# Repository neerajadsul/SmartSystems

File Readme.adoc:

# Temperature, Humidity, Ambient Light Monitoring
ifdef::env-name[:relfilesuffix: .adoc]

The goal of this project is to design a temperature and humidity monitoring system for indoor home usage.

## Specifications
. Monitor the temperature (T) in deg celsius with accuracy of better than 1%.
. Monitor the humidity (RH) in %RH (relative humidity) with accuracy of better than 5%.
. Monitor the ambient light in relative lux (LUX) with respect to dark.
. Capable of recording the T, RH, LUX at least once every 30 seconds.
. Records T, RH, LUX in a database.
. Presents T, RH, LUX data as a time-series via a web-interface.
. The web-interface is accesible atleast within the intra-net.

## System Design
A block diamgram of the system is shown in the figure below.

image::SensorNetwork/figures/SystemBlockDiagram.svg[Home Monitoring Systems Block Diagram]

## Hardware Design
The sensor board has Sensirion SHTC3 temperature and humidity sensor.
The board is designed to fit on top or under of the Raspberry Pi Pico W (PicoW).

image::SensorNetwork/figures/board_views.svg["Sensorboard for Temperature, Humidity and Ambient Light"]

## Software Design

### Monitoring Server
The monitoring server is deployed on a Raspberry Pi 400.
The sensor node communicates to a Python Django based web-app which can receive data on port 8080.
The web app stores data in a SQLite database. The database backup is scheduled for everyday on a internal network attached storage.

#### Web API Specifications

Web API specifications are documented in xref:SensorNetwork/WebAPISpecifications.adoc[Web API Specifications]
# Web API Specifications

## Sensor Node
### Send Monitoring Data Point
* Sensor Node sends the data with a `<POST>` request.
* Endpoint: `/thlmonitor/sensor_data`
* Send data in as Python dictionary. Individual fields are listed below:
** `location` sent as a tuple of grid co-ordinates as per the sensor grid specifications
** `timestamp` sent as a of tuple of `time.localtime()`
** Temperature `T` sent as a number with one decimal precision.
** Relative Humidity `RH` sent as a an integer number between [0, 100].
** Ambient Light intensity `LUX` sent as a number with one decimal precision.

For example:
Ground floor, living room
[source, json] 
{"location":'0E4',"timestamp":(2023, 1, 15, 16, 47, 39, 6, 15),"T":23.5,"RH":50.5,"LUX":34.2}
OR
{"location":'GE4',"timestamp":(2023, 1, 15, 16, 47, 39, 6, 15),"T":23.5,"RH":50.5,"LUX":34.2}

First floor, N Office room
[source, json]
{"location":'1A6',"timestamp":(2023, 1, 15, 16, 47, 39, 6, 15),"T":23.5,"RH":50.5,"LUX":34.2}
OR
{"location":'FA6',"timestamp":(2023, 1, 15, 16, 47, 39, 6, 15),"T":23.5,"RH":50.5,"LUX":34.2}

### Get Current Time from Server
* Sensor requests current time with a `<GET>` request.
* Endpoint: `/thlmonitor/sensor_data`
** Data sent as number of seconds from epoch. 

### Example Sensor Grid Specifications

image::SensorNetwork/figures/SensorGridSpecification.svg[Sensor Grid for a Typical House]

## User Front End for Home Monitoring
[TBD]

### Sensor Node
Programmers model for the sensor board is shown in following figure:

image::SensorNetwork/figures/FirmwareProgrammersModel.svg[SensorBoard connections to Pico W]

* Each sensor node consists of a PicoW as controller and THL sensor board.
* Each sensor node has a location tag to uniquely identify the location.
* PicoW sets up time of internal RTC clock
* PicoW uses MicroPython with urequest library
* Each of the Sensirion T/RH and LiteOn Ambient light sensor communicates with PicoW via I2C interface.
* The sensor node acquires T, RH and LUX data every 30 seconds and puts it in a queue.
* The node attempts to send the data in queue to the server in JSON format specified above.
If successful the datapoint is dequeued, else attempted again.

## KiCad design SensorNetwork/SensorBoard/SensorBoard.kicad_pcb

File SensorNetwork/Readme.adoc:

# Temperature, Humidity, Ambient Light Monitoring
ifdef::env-name[:relfilesuffix: .adoc]

The goal of this project is to design a temperature and humidity monitoring system for indoor home usage.

## Specifications
. Monitor the temperature (T) in deg celsius with accuracy of better than 1%.
. Monitor the humidity (RH) in %RH (relative humidity) with accuracy of better than 5%.
. Monitor the ambient light in relative lux (LUX) with respect to dark.
. Capable of recording the T, RH, LUX at least once every 30 seconds.
. Records T, RH, LUX in a database.
. Presents T, RH, LUX data as a time-series via a web-interface.
. The web-interface is accesible atleast within the intra-net.

## System Design
A block diamgram of the system is shown in the figure below.

image::figures/SystemBlockDiagram.svg[Home Monitoring Systems Block Diagram]

## Hardware Design
The sensor board has Sensirion SHTC3 temperature and humidity sensor.
The board is designed to fit on top or under of the Raspberry Pi Pico W (PicoW).

image::figures/THLSensorBoard.png["Sensorboard for Temperature, Humidity and Ambient Light", 150]

image::figures/SensorBoardPinout.svg[Sensor Board Pinout]

## Software Design

### Monitoring Server
The monitoring server is deployed on a Raspberry Pi 400.
The sensor node communicates to a Python Flask based web-app which can receive data on port 6161.
The web app stores data in a SQLite database. The database backup is scheduled for everyday on a internal network attached storage.

#### Web API Specifications

Web API specifications are documented in xref:WebAPISpecifications.adoc[Web API Specifications]

### Sensor Node
Programmers model for the sensor board is shown in following figure:

image::figures/FirmwareProgrammersModel.svg[SensorBoard connections to Pico W]

* Each sensor node consists of a PicoW as controller and THL sensor board.
* Each sensor node has a location tag to uniquely identify the location.
* PicoW sets up time of internal RTC clock
* PicoW uses MicroPython with urequest library
* Each of the Sensirion T/RH and LiteOn Ambient light sensor communicates with PicoW via I2C interface.
* The sensor node acquires T, RH and LUX data every 30 seconds and puts it in a queue.
* The node attempts to send the data in queue to the server in JSON format specified above.
If successful the datapoint is dequeued, else attempted again.

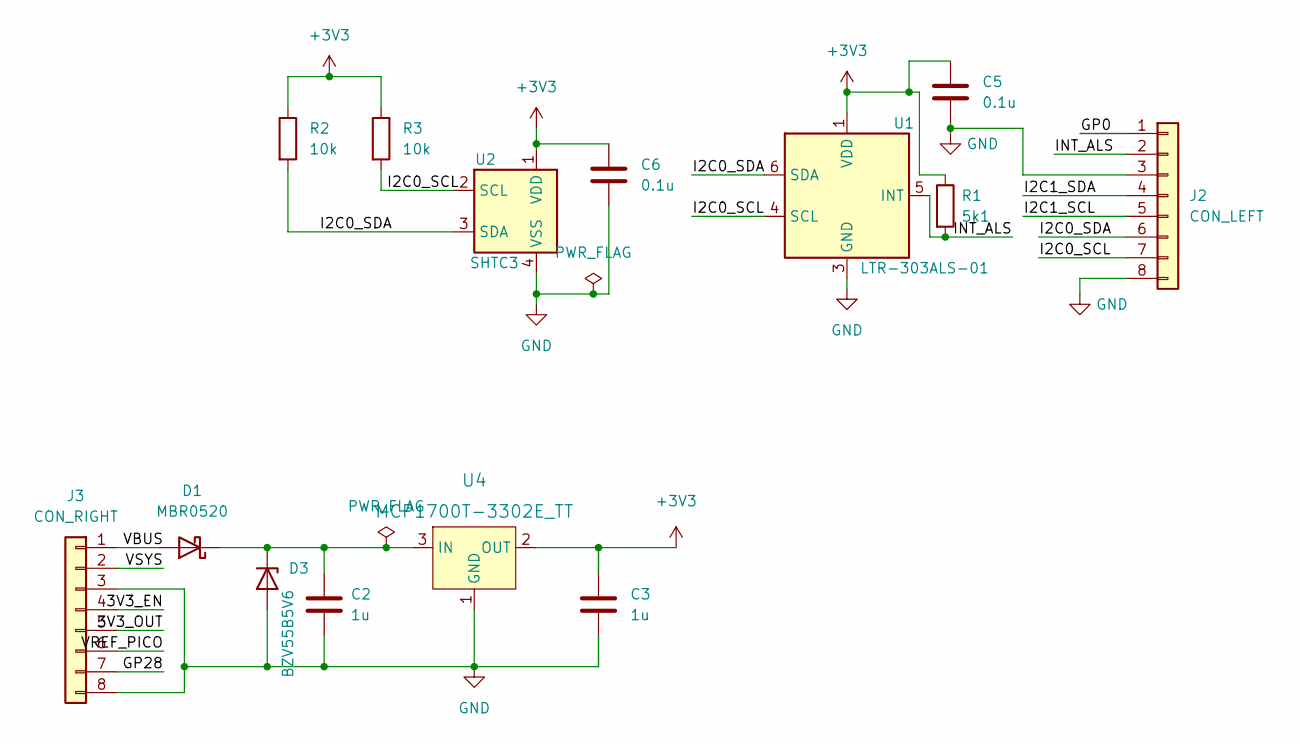
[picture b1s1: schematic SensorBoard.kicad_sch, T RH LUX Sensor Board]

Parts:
C2, C3: 1u; C_0805_2012Metric
C5, C6: 0.1u; C_0805_2012Metric
D1: MBR0520; D_SOD-123
D3: BZV55B5V6; D_MiniMELF
J2: CON_LEFT; PinHeader_1x08_P2.54mm_Vertical
J3: CON_RIGHT; PinHeader_1x08_P2.54mm_Vertical
R1: 5k1; R_0603_1608Metric
R2, R3: 10k; R_0603_1608Metric
U1: LTR-303ALS-01; Lite-On_LTR-303ALS-01
U2: SHTC3; Sensirion_DFN-4-1EP_2x2mm_P1mm_EP0.7x1.6mm
U4: MCP1700T-3302E_TT; SOT-23-3; MPN MCP1700T-3302E/TT; Digi-Key_PN MCP1700T3302ETTCT-ND

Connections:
+3V3: C3.1, C5.1, C6.1, R1.1, R2.1, R3.1, U1.1 (VDD), U2.1 (VDD), U4.2 (OUT)
/3V3_EN: J3.4
/3V3_OUT: J3.5
/GP0: J2.1
/GP28: J3.7
/I2C0_SCL: J2.7, R3.2, U1.4 (SCL), U2.2 (SCL)
/I2C0_SDA: J2.6, R2.2, U1.6 (SDA), U2.3 (SDA)
/I2C1_SCL: J2.5
/I2C1_SDA: J2.4
/INT_ALS: J2.2, R1.2, U1.5 (INT)
/VBUS: D1.2 (A), J3.1
/VREF_PICO: J3.6
/VSYS: J3.2
GND: C2.2, C3.2, C5.2, C6.2, D3.2 (A), J2.3, J2.8, J3.3, J3.8, U1.3 (GND), U2.4 (VSS), U4.1 (GND)
unnamed: C2.1, D1.1 (K), D3.1 (K), U4.3 (IN)

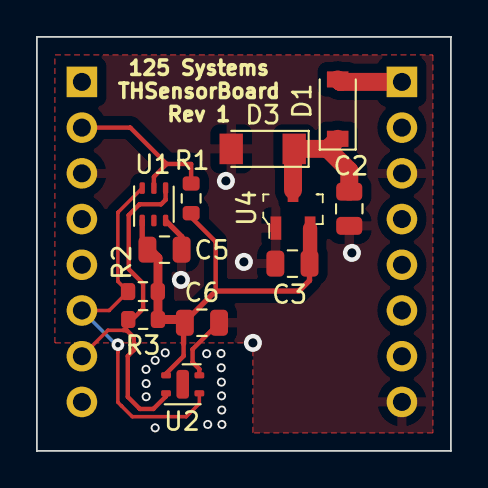
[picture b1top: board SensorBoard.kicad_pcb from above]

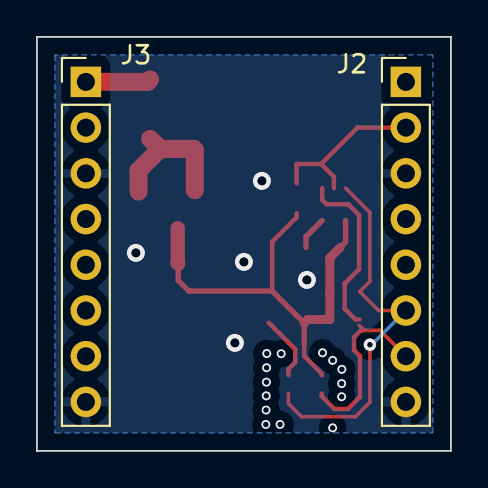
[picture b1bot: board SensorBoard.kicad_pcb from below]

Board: 2 copper layers, 23.0 x 23.0 mm, 14 parts (2 on the bottom side), 7 nets.

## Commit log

2022-10-07 ignores OS hidden files
2022-10-12 working T, H reading from SH11x
2022-12-10 Starter draft of the sensor board
2023-01-04 Sensor board routed and checked
2023-01-04 Sensor board HTML interactive BOM
2023-01-09 Documentation and specifications
2023-01-10 Starter project and app
2023-01-10 Customises home page, dependencies file
2023-01-13 Documentions connections, local archive of 3d models, updates ibom
2023-01-16 Updates specifications for Web API, system design, programmers model
2023-01-16 Implements connection to wifi using config from text file
2023-01-18 Sensor drivers, ALS works, SHT does not
2023-01-18 Corrects GPIO pin reference and adds correponding note
2023-01-20 SHT and LTR sensor functions with CircuitPython
2023-01-20 Removes prototype scripts to individually work the sensors
2023-01-23 Applies 125 Systems website theme
2023-03-01 view for getting sensor data
2023-03-01 updates url for endpoint to receive sensor data
2023-03-01 data models to store environmental data and sensor location
2023-03-01 migrations for evironmental data and sensor location
2023-03-01 ignore SQLite DB file from Git
2023-04-26 Models to store Temperature, Humidity and Lighting data
2023-04-26 Registers models for Temperature, Humidity and Lighting data and sensor locations.
2023-04-26 Mechanism to receive sensor data point
2023-04-26 Upgrades packages to latest available.
2023-04-26 Ignore PyCharm files.
2023-04-26 Maps base url to index view
2023-04-26 Draw schematic map of ground and first floor with HTML canvas
2023-04-26 Favicons for variety of browsers.
2023-04-26 Draws overlay of rooms layout and sensor grid.
2023-04-26 Refactors X and Y grid step delta to constant variable.
2023-04-27 Ability to show measurements on grid coordinates.
2023-04-27 Adds click event listeners for floor layouts
2023-05-24 Fixes schematic and PCB, update corresponding figures
2023-05-24 Update system design documents
2023-05-25 Sends data obtained via I2C to server
2023-05-25 Updates format for sending sensor location to avoid conflict with tuple syntax
2023-06-30 remove SSID name
2024-04-11 Move Readme to root directory.
2024-04-11 Refactor steps into functions.
2024-04-11 Config changes to KiCAD 8
2024-04-11 Update links to figure after moving readme location.
2024-04-11 Update board view to include all in a row.
2024-04-11 Update docs for end-point.
2024-04-11 Ignore VSCode directory.
2024-04-12 Send latest THL data to the template using json_script filter.
2024-04-17 Change project structure.
2024-04-17 Document webapi specs on main Readme.
2024-04-17 Fix figure location.
2024-04-17 Update dependencies.
2024-04-17 Update dependencies to latest possible.
2024-04-17 Rules for Github linguist.
2024-08-13 Update diagrams for docs.
2024-08-13 Update dependencies versions.
